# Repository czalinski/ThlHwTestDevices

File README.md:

# ThlHwTestDevices

KiCad designs, firmware and documentation for circuits that support testing of
electrical hardware, such as HASS and HALT testing.

Each design lives in its own folder under [`circuits/`](circuits/). Released
versions get separate folders with a version suffix (for example `V1p3` is
version 1.3), so every released version stays available side by side.

## License

Original work in this repository — the circuit designs, firmware and
documentation — is released under the [MIT License](LICENSE).

### Third-party files

The following are **not** covered by the MIT License. They remain under the
terms set by their original authors or providers:

* **`KiCad/` part libraries** (`footprints/`, `symbols/`,
  `SamacSys_Parts.pretty/`). Many of these footprints and symbols were
  downloaded from part-library services such as SnapEDA and SamacSys
  (Component Search Engine), or copied from the KiCad standard libraries.
  Check the provider's terms before redistributing them.
* **`Support/*.rar`**: setup and utility files for the T-962 reflow oven,
  included for convenience.
* **FatFs** in `circuits/ParasiticV1p0/firmware/lib/fatfs/`, by ChaN, under
  its own BSD-style license
  ([LICENSE.txt](circuits/ParasiticV1p0/firmware/lib/fatfs/LICENSE.txt)).

The PCB files (`*.kicad_pcb`) contain embedded copies of some of these
footprints, as all KiCad boards do. If you are a rights holder and believe a
file here should not be distributed, please open an issue.

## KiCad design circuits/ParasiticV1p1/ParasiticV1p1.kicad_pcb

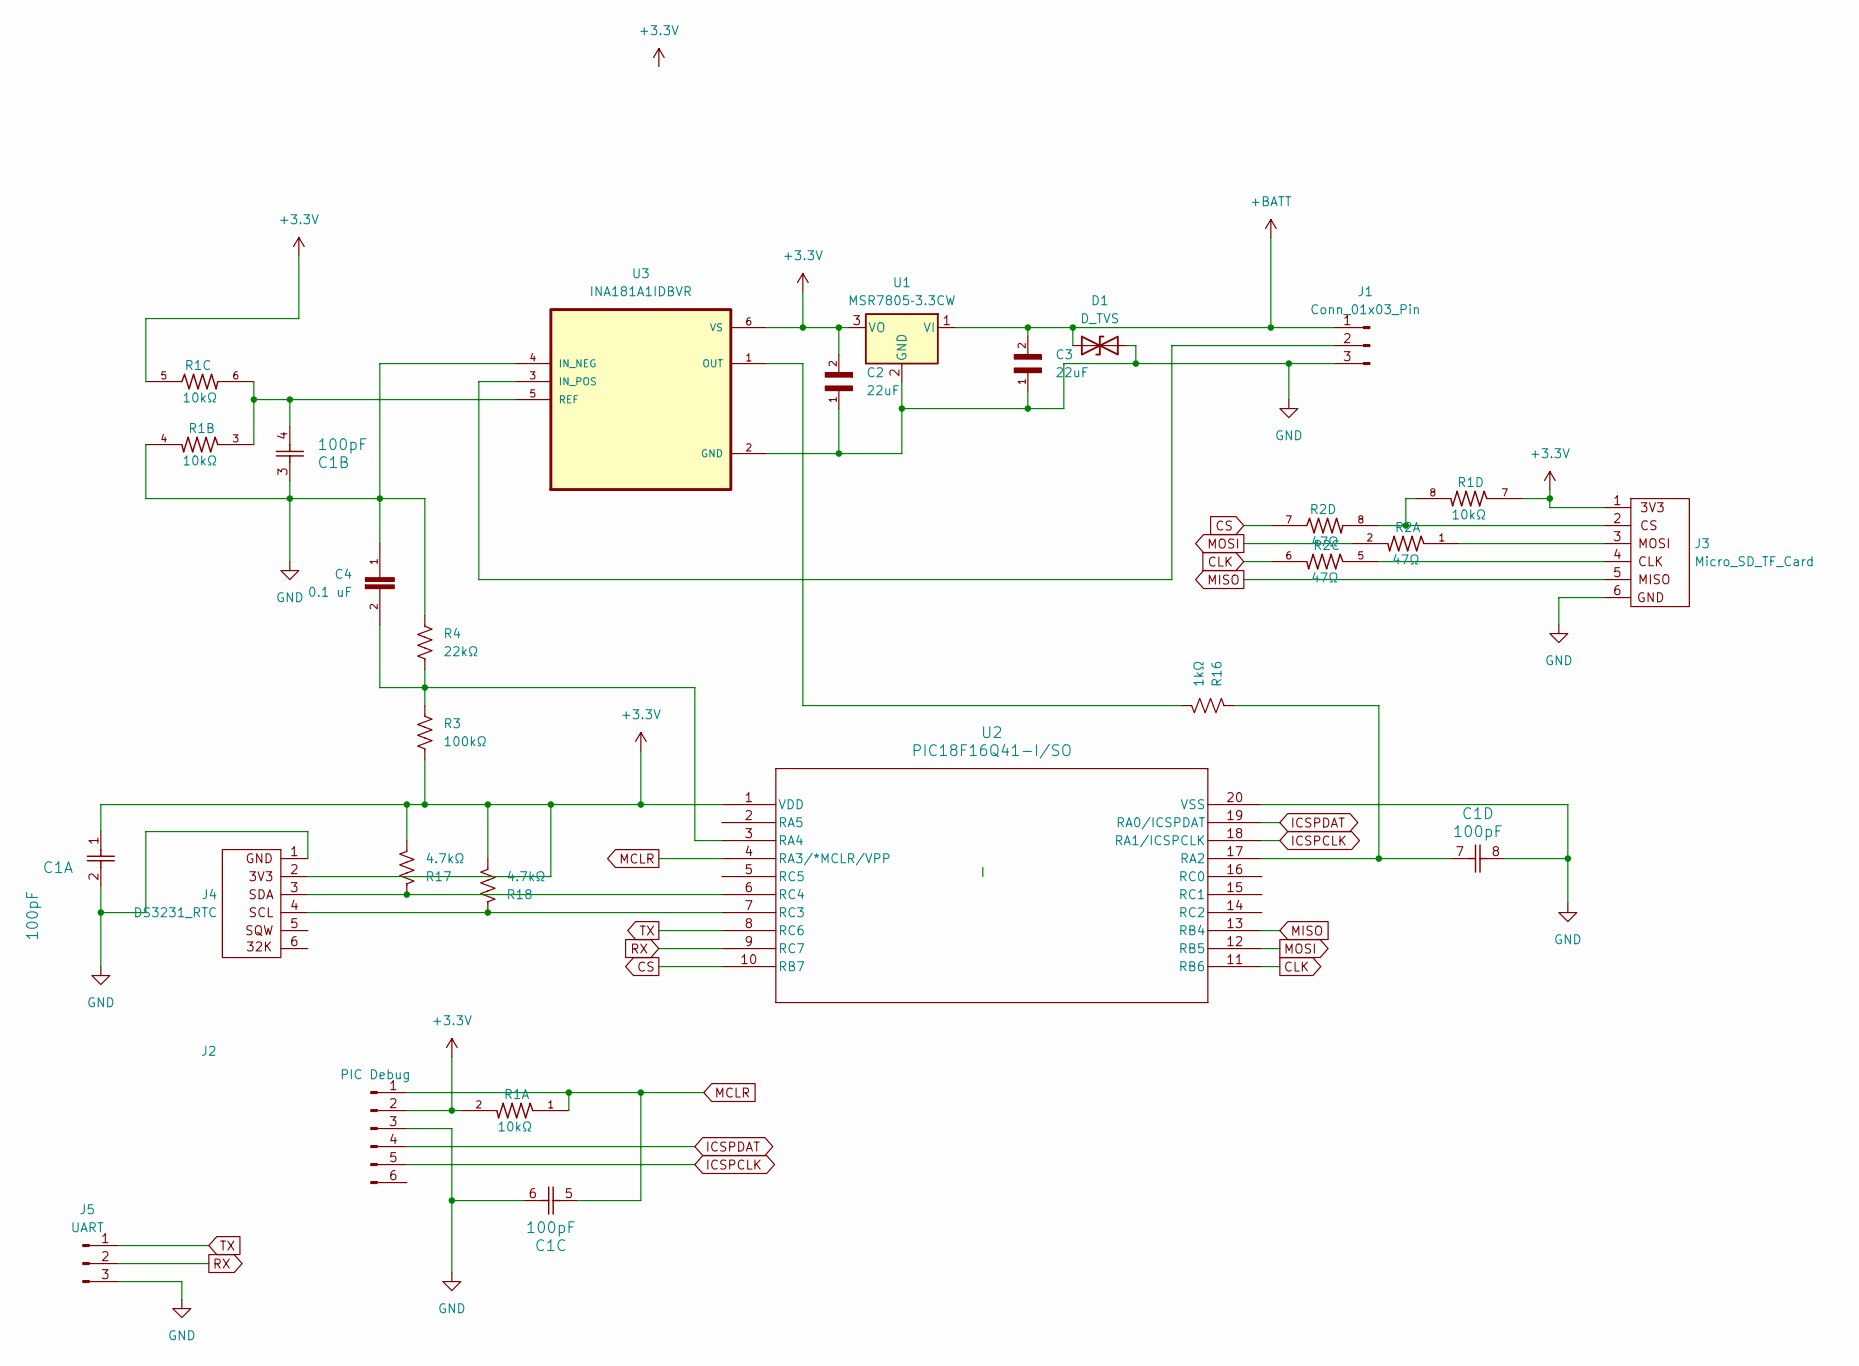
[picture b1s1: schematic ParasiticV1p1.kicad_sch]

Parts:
C1: 100pF; CAP_CA0612_3P2X1P6_YAG
C2, C3: 22uF; CAPC3225X270N
C4: 0.1 uF; DecouplingCapSMDLg
D1: D_TVS; D_SMC_Handsoldering
J1: Conn_01x03_Pin; PinHeader_1x03_P2.54mm_Vertical
J2: PIC Debug; PinHeader_1x06_P2.54mm_Horizontal
J3: Micro_SD_TF_Card
J4: DS3231_RTC; PinHeader_1x06_P2.54mm_Vertical
J5: UART; PinHeader_1x03_P2.54mm_Vertical
R1: 10kΩ; RESCAV80P320X160X70-8N
R2: 47Ω; RESCAV80P320X160X70-8N
R3: 100kΩ; RES_1206
R4: 22kΩ; RES_1206
R16: 1kΩ; RES_1206
R17, R18: 4.7kΩ; RES_1206
U1: MSR7805‑3.3CW; 3-SIP
U2: PIC18F16Q41-I/SO; SOIC20_SO_MCH
U3: INA181A1IDBVR; SOT95P280X145-6N

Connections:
+3.3V: C1.1, C2.2, J2.2, J3.1 (3V3), J4.2 (CS), R1.2, R1.5, R1.7, R3.2, R17.2, R18.2, U1.3 (VO), U2.1 (VDD), U3.6 (VS)
+BATT: C3.2, D1.1 (A1), J1.1, U1.1 (VI)
CLK: R2.6, U2.11 (RB6)
CS: R2.7, U2.10 (RB7)
GND: C1.2, C1.3, C1.6, C1.8, C2.1, C3.1, C4.1, D1.2 (A2), J1.3, J2.3, J3.6 (GND), J4.1 (3V3), J5.3, R1.4, R4.1, U1.2 (GND), U2.20 (VSS), U3.2 (GND), U3.4 (IN_NEG)
ICSPCLK: J2.5, U2.18 (RA1/ICSPCLK)
ICSPDAT: J2.4, U2.19 (RA0/ICSPDAT)
MCLR: C1.5, J2.1, R1.1, U2.4 (RA3/*MCLR/VPP)
MISO: J3.5 (MISO), U2.13 (RB4)
MOSI: R2.2, U2.12 (RB5)
unnamed: J1.2, U3.3 (IN_POS)
unnamed: J3.4 (CLK), R2.5
unnamed: J3.2 (CS), R1.8, R2.8
unnamed: J3.3 (MOSI), R2.1
unnamed: J4.4 (CLK), R18.1, U2.7 (RC3)
unnamed: J4.3 (MOSI), R17.1, U2.6 (RC4)
unnamed: C1.7, R16.1, U2.17 (RA2)
unnamed: C4.2, R3.1, R4.2, U2.3 (RA4)
unnamed: R16.2, U3.1 (OUT)
unnamed: C1.4, R1.3, R1.6, U3.5 (REF)
RX: J5.2, U2.9 (RC7)
TX: J5.1, U2.8 (RC6)

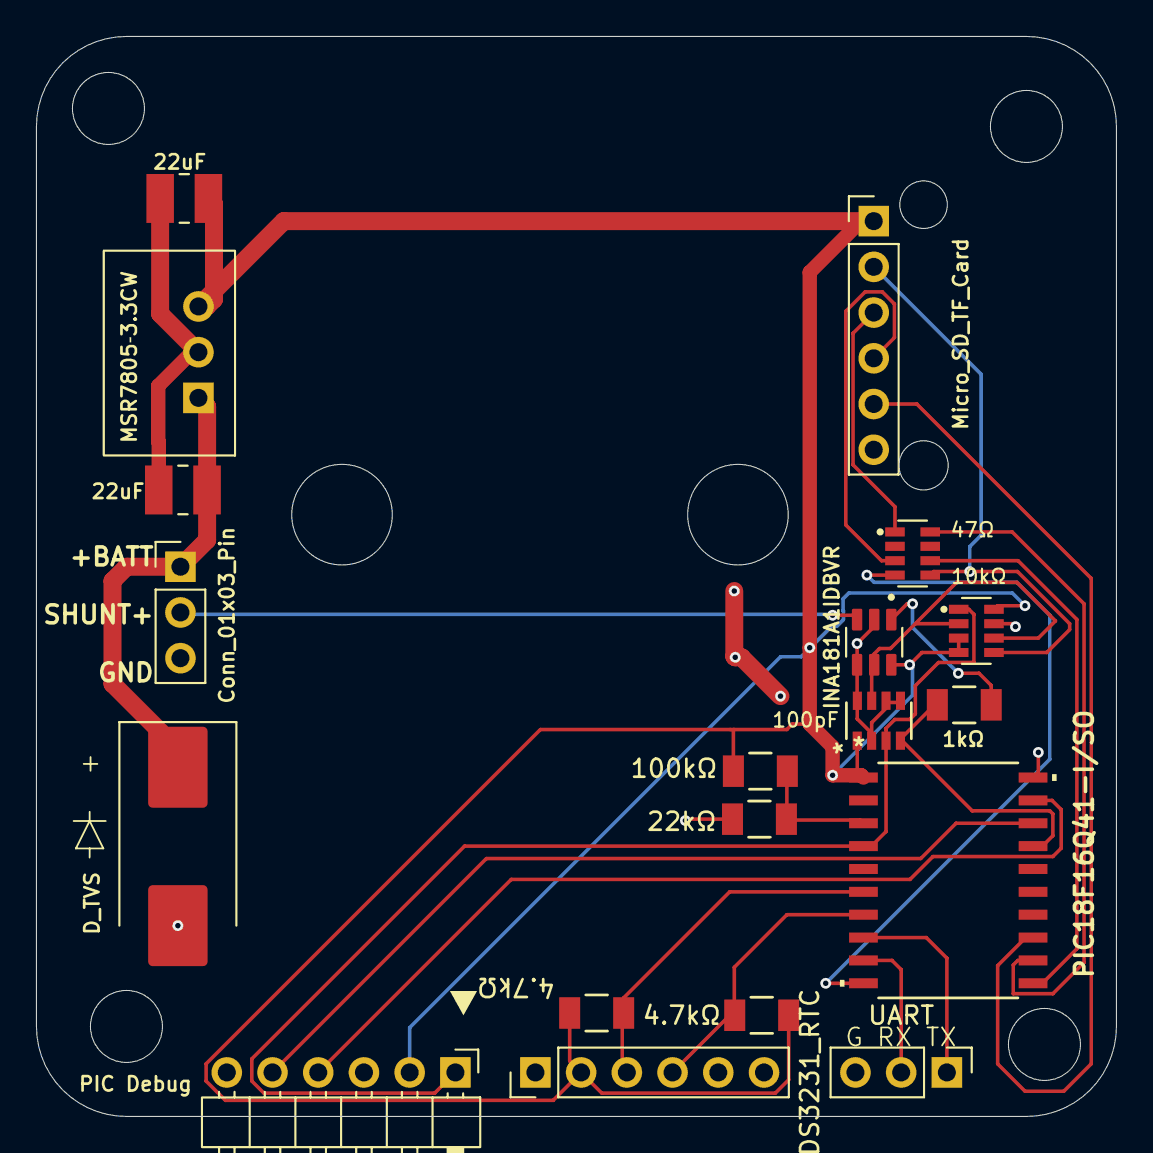
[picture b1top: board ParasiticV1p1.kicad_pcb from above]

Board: 2 copper layers, 60.0 x 60.0 mm, 19 parts (0 on the bottom side), 22 nets.

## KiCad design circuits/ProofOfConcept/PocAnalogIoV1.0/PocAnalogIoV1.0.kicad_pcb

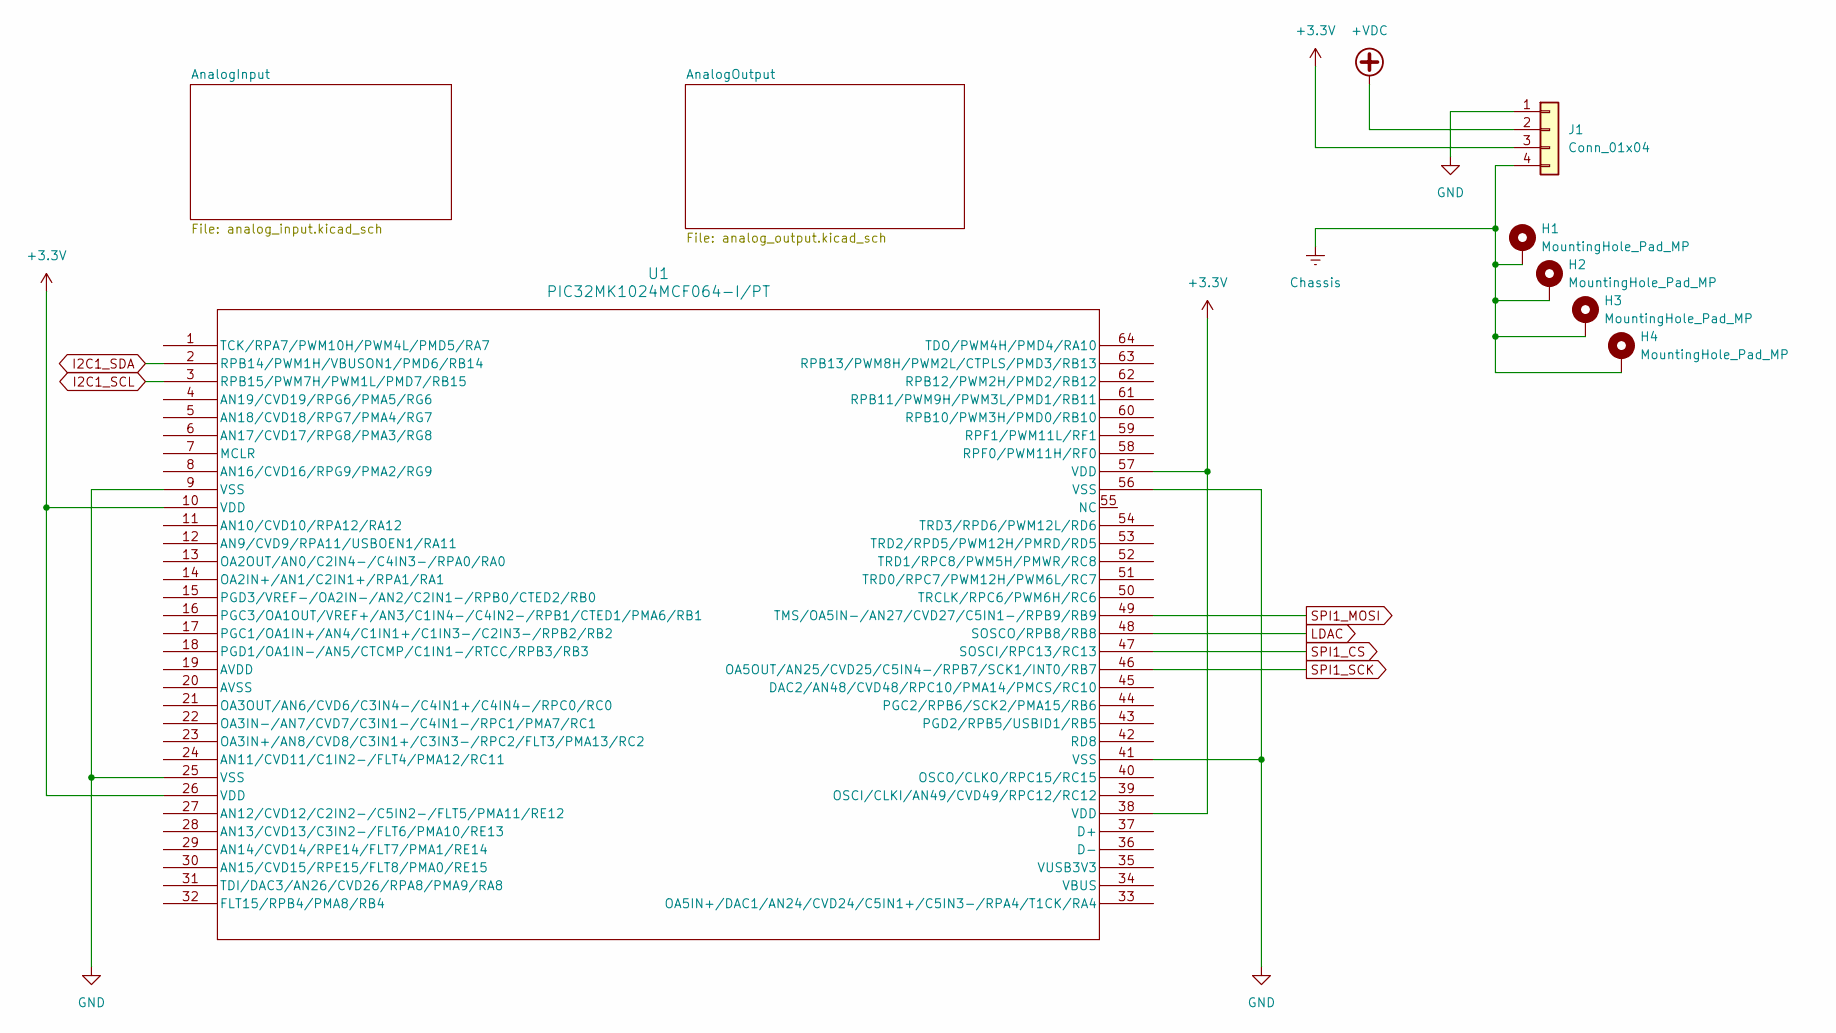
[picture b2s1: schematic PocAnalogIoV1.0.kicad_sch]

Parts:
H1, H2, H3, H4: MountingHole_Pad_MP; MountingHole_3.2mm_M3_Pad_Via
J1: Conn_01x04; PinHeader_1x04_P2.54mm_Vertical
U1: PIC32MK1024MCF064-I/PT; PIC64_Breakout

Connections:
+3.3V: J1.3, U1.10 (VDD), U1.26 (VDD), U1.38 (VDD), U1.57 (VDD); also elsewhere on the board
+VDC: J1.2; also elsewhere on the board
Chassis: H1.1 (MP_1), H2.1 (MP_1), H3.1 (MP_1), H4.1 (MP_1), J1.4
GND: J1.1, U1.9 (VSS), U1.25 (VSS), U1.41 (VSS), U1.56 (VSS); also elsewhere on the board
I2C1_SCL: U1.3 (RPB15/PWM7H/PWM1L/PMD7/RB15); also elsewhere on the board
I2C1_SDA: U1.2 (RPB14/PWM1H/VBUSON1/PMD6/RB14); also elsewhere on the board
LDAC: U1.48 (SOSCO/RPB8/RB8); also elsewhere on the board
SPI1_CS: U1.47 (SOSCI/RPC13/RC13); also elsewhere on the board
SPI1_MOSI: U1.49 (TMS/OA5IN-/AN27/CVD27/C5IN1-/RPB9/RB9); also elsewhere on the board
SPI1_SCK: U1.46 (OA5OUT/AN25/CVD25/C5IN4-/RPB7/SCK1/INT0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); also elsewhere on the board

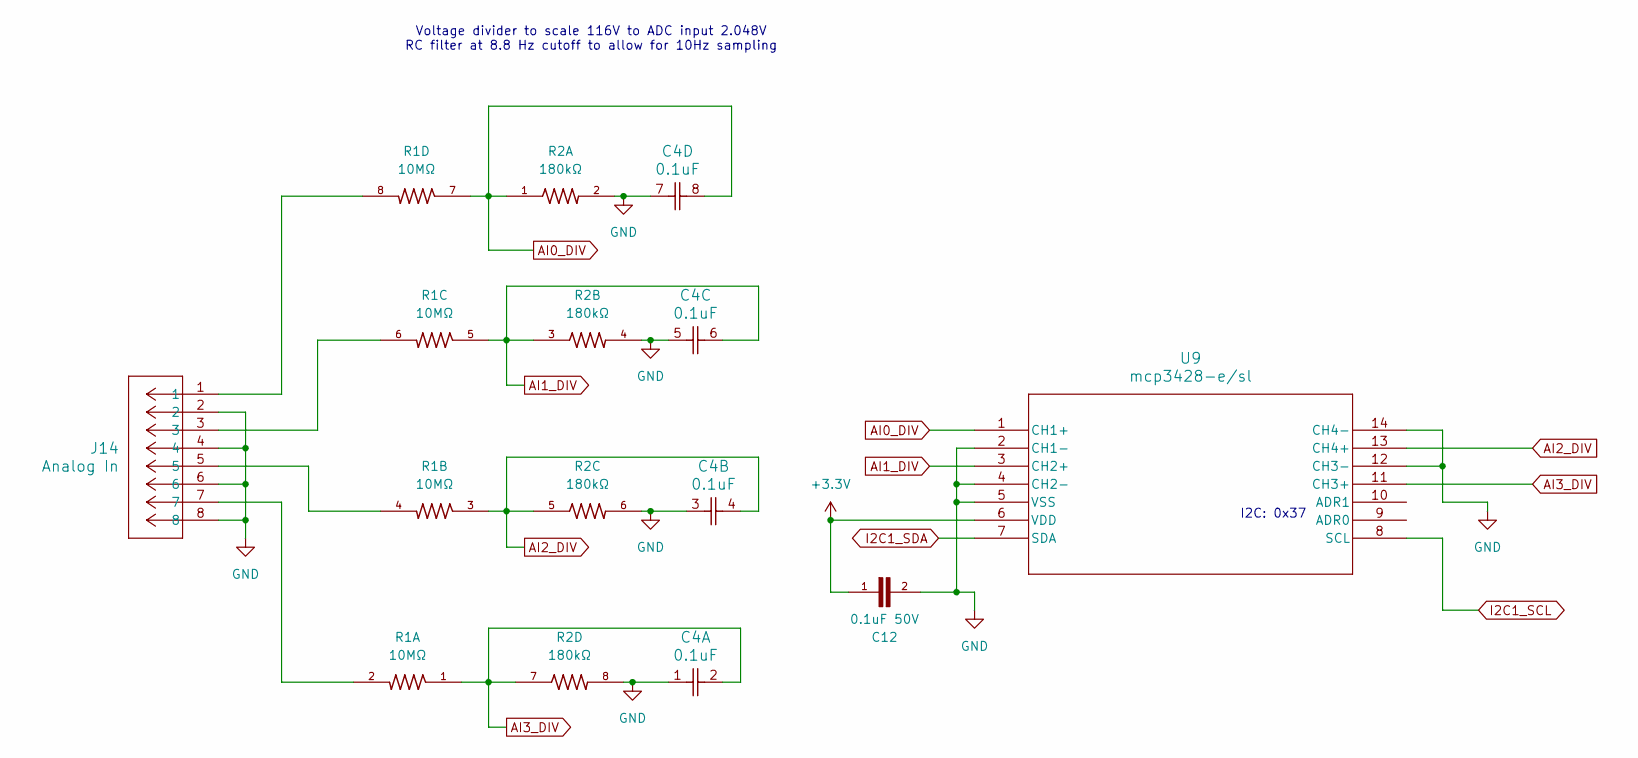
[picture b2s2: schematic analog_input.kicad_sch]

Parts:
C4: 0.1uF; CAP_CA0612_3P2X1P6_YAG
C12: 0.1uF 50V; CAPC2012X70
J14: Analog In; CONN_1989803_PXC
R1: 10MΩ; RESCAV80P320X160X70-8N
R2: 180kΩ; RESCAV80P320X160X70-8N
U9: mcp3428-e/sl; SOIC14-N_MC_MCH

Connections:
+3.3V: C12.1, U9.6 (VDD); also elsewhere on the board
AI0_DIV: C4.8, R1.7, R2.1, U9.1 (CH1+)
AI1_DIV: C4.6, R1.5, R2.3, U9.3 (CH2+)
AI2_DIV: C4.4, R1.3, R2.5, U9.13 (CH4+)
AI3_DIV: C4.2, R1.1, R2.7, U9.11 (CH3+)
GND: C4.1, C4.3, C4.5, C4.7, C12.2, J14.2, J14.4, J14.6, J14.8, R2.2, R2.4, R2.6, R2.8, U9.2 (CH1-), U9.4 (CH2-), U9.5 (VSS), U9.12 (CH3-), U9.14 (CH4-); also elsewhere on the board
I2C1_SCL: U9.8 (SCL); also elsewhere on the board
I2C1_SDA: U9.7 (SDA); also elsewhere on the board
unnamed: J14.1, R1.8
unnamed: J14.3, R1.6
unnamed: J14.5, R1.4
unnamed: J14.7, R1.2

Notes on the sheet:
I2C: 0x37
Voltage divider to scale 116V to ADC input 2.048V RC filter at 8.8 Hz cutoff to allow for 10Hz sampling

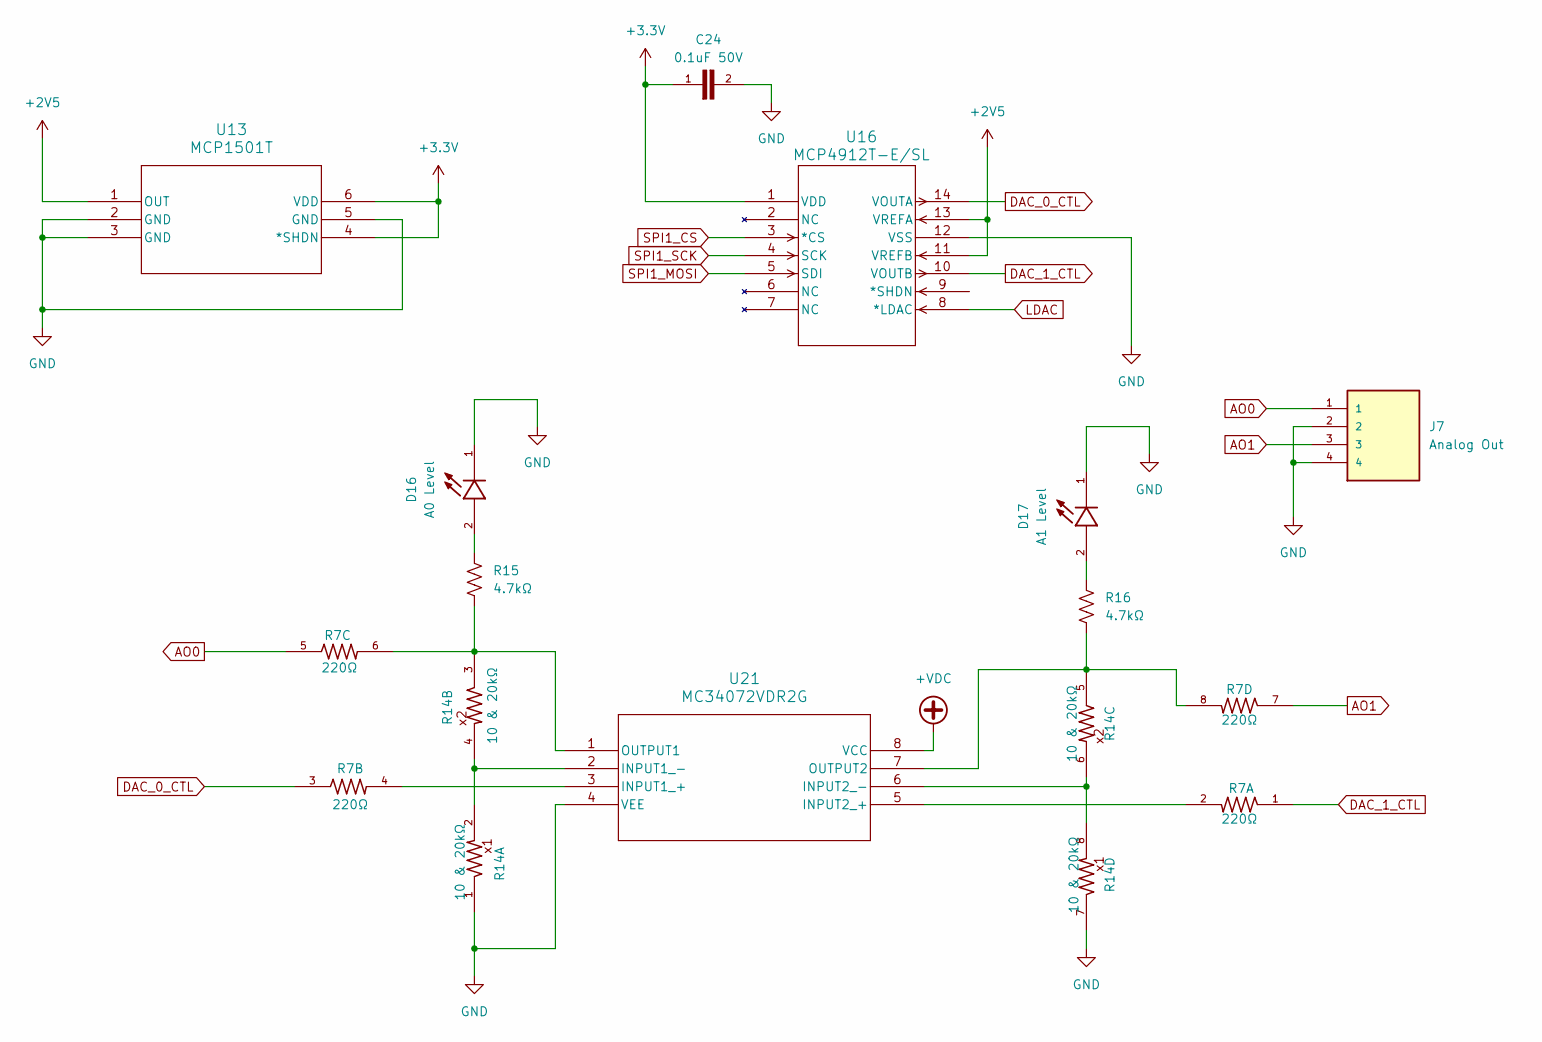
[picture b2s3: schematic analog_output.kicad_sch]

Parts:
C24: 0.1uF 50V; CAPC2012X70
D16: A0 Level; LED_LTST-C170GKT; PARTREV I
D17: A1 Level; LED_LTST-C170GKT; PARTREV I
J7: Analog Out; TE_1985218; PARTREV 29.03.2021
R7: 220Ω; RESCAV80P320X160X70-8N
R14: 10 & 20kΩ; RESCAV80P320X160X70-8N
R15, R16: 4.7kΩ; RES_1206
U13: MCP1501T; SOT-23_OT&slash_OTY_MCH
U16: MCP4912T-E/SL; SOIC14-N_MC_MCH
U21: MC34072VDR2G; SOIC8_ONS

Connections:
+2V5: U13.1 (OUT), U16.11 (VREFB), U16.13 (VREFA)
+3.3V: C24.1, U13.4 (*SHDN), U13.6 (VDD), U16.1 (VDD); also elsewhere on the board
+VDC: U21.8 (VCC); also elsewhere on the board
AO0: J7.1, R7.5
AO1: J7.3, R7.7
DAC_0_CTL: R7.3, U16.14 (VOUTA)
DAC_1_CTL: R7.1, U16.10 (VOUTB)
GND: C24.2, D16.1, D17.1, J7.2, J7.4, R14.1, R14.7, U13.2 (GND), U13.3 (GND), U13.5 (GND), U16.12 (VSS), U21.4 (VEE); also elsewhere on the board
LDAC: U16.8 (*LDAC); also elsewhere on the board
unnamed: D16.2, R15.1
unnamed: D17.2, R16.1
unnamed: R7.4, U21.3 (INPUT1_+)
unnamed: R14.2, R14.4, U21.2 (INPUT1_-)
unnamed: R7.2, U21.5 (INPUT2_+)
unnamed: R14.6, R14.8, U21.6 (INPUT2_-)
unnamed: R7.6, R14.3, R15.2, U21.1 (OUTPUT1)
unnamed: R7.8, R14.5, R16.2, U21.7 (OUTPUT2)
SPI1_CS: U16.3 (*CS); also elsewhere on the board
SPI1_MOSI: U16.5 (SDI); also elsewhere on the board
SPI1_SCK: U16.4 (SCK); also elsewhere on the board

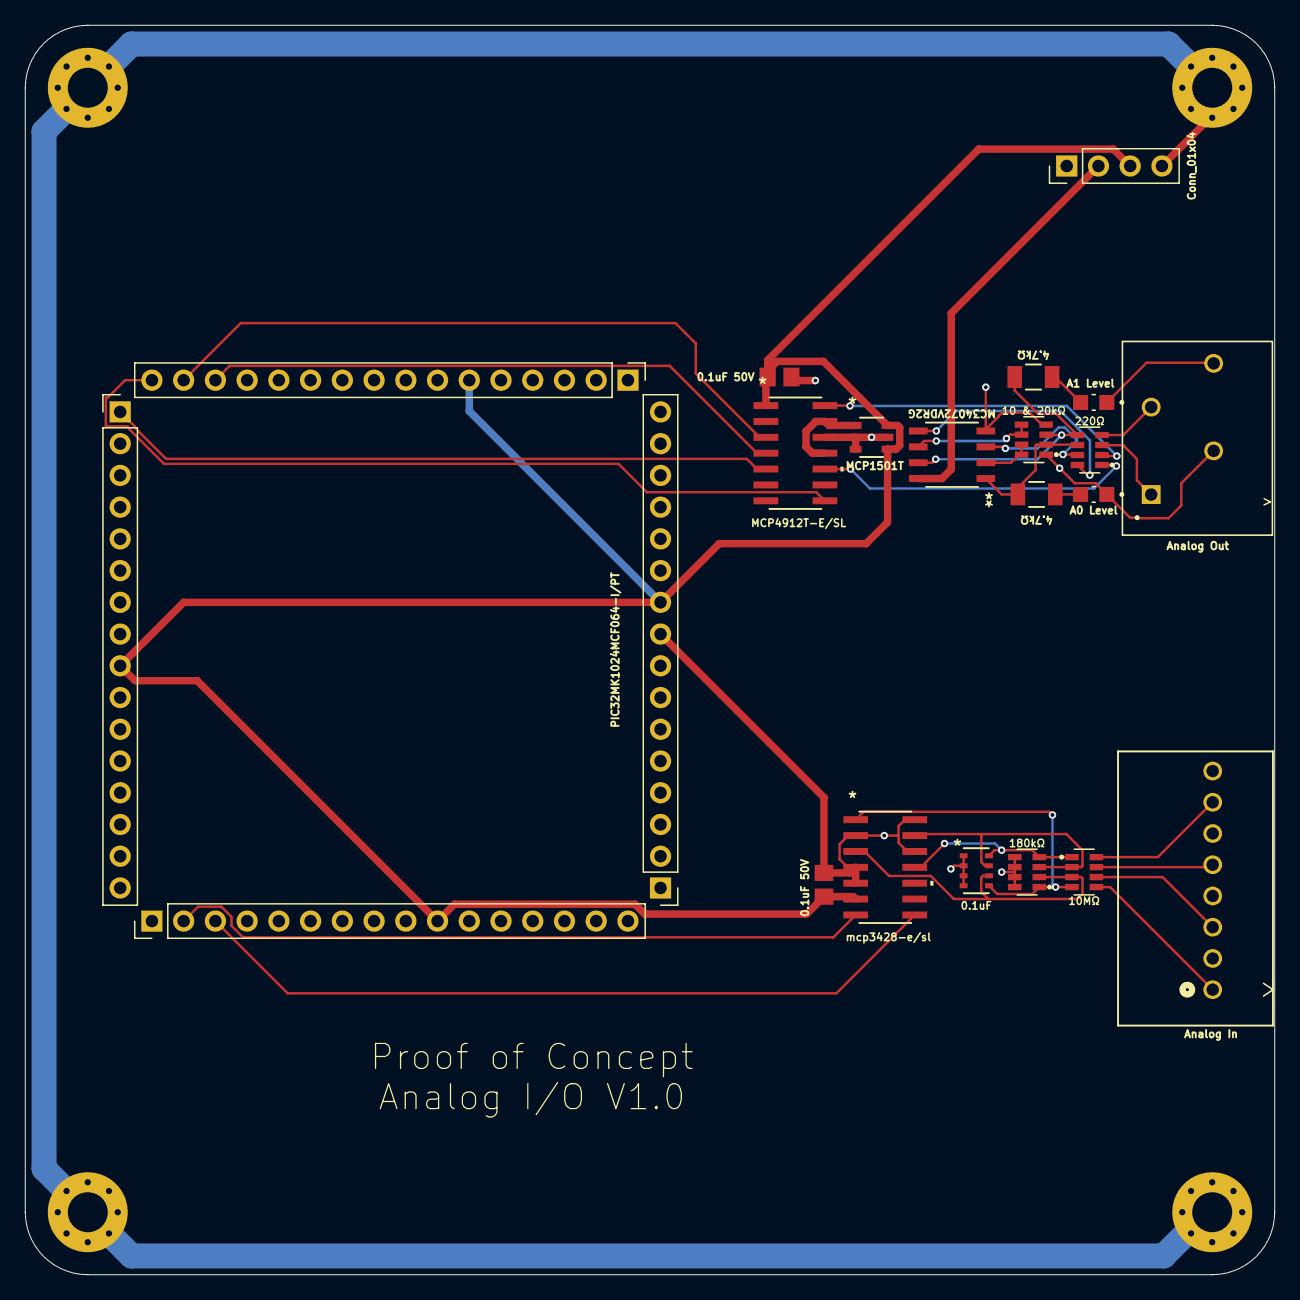
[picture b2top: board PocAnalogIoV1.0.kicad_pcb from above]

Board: 2 copper layers, 100.0 x 100.0 mm, 23 parts (0 on the bottom side), 31 nets.

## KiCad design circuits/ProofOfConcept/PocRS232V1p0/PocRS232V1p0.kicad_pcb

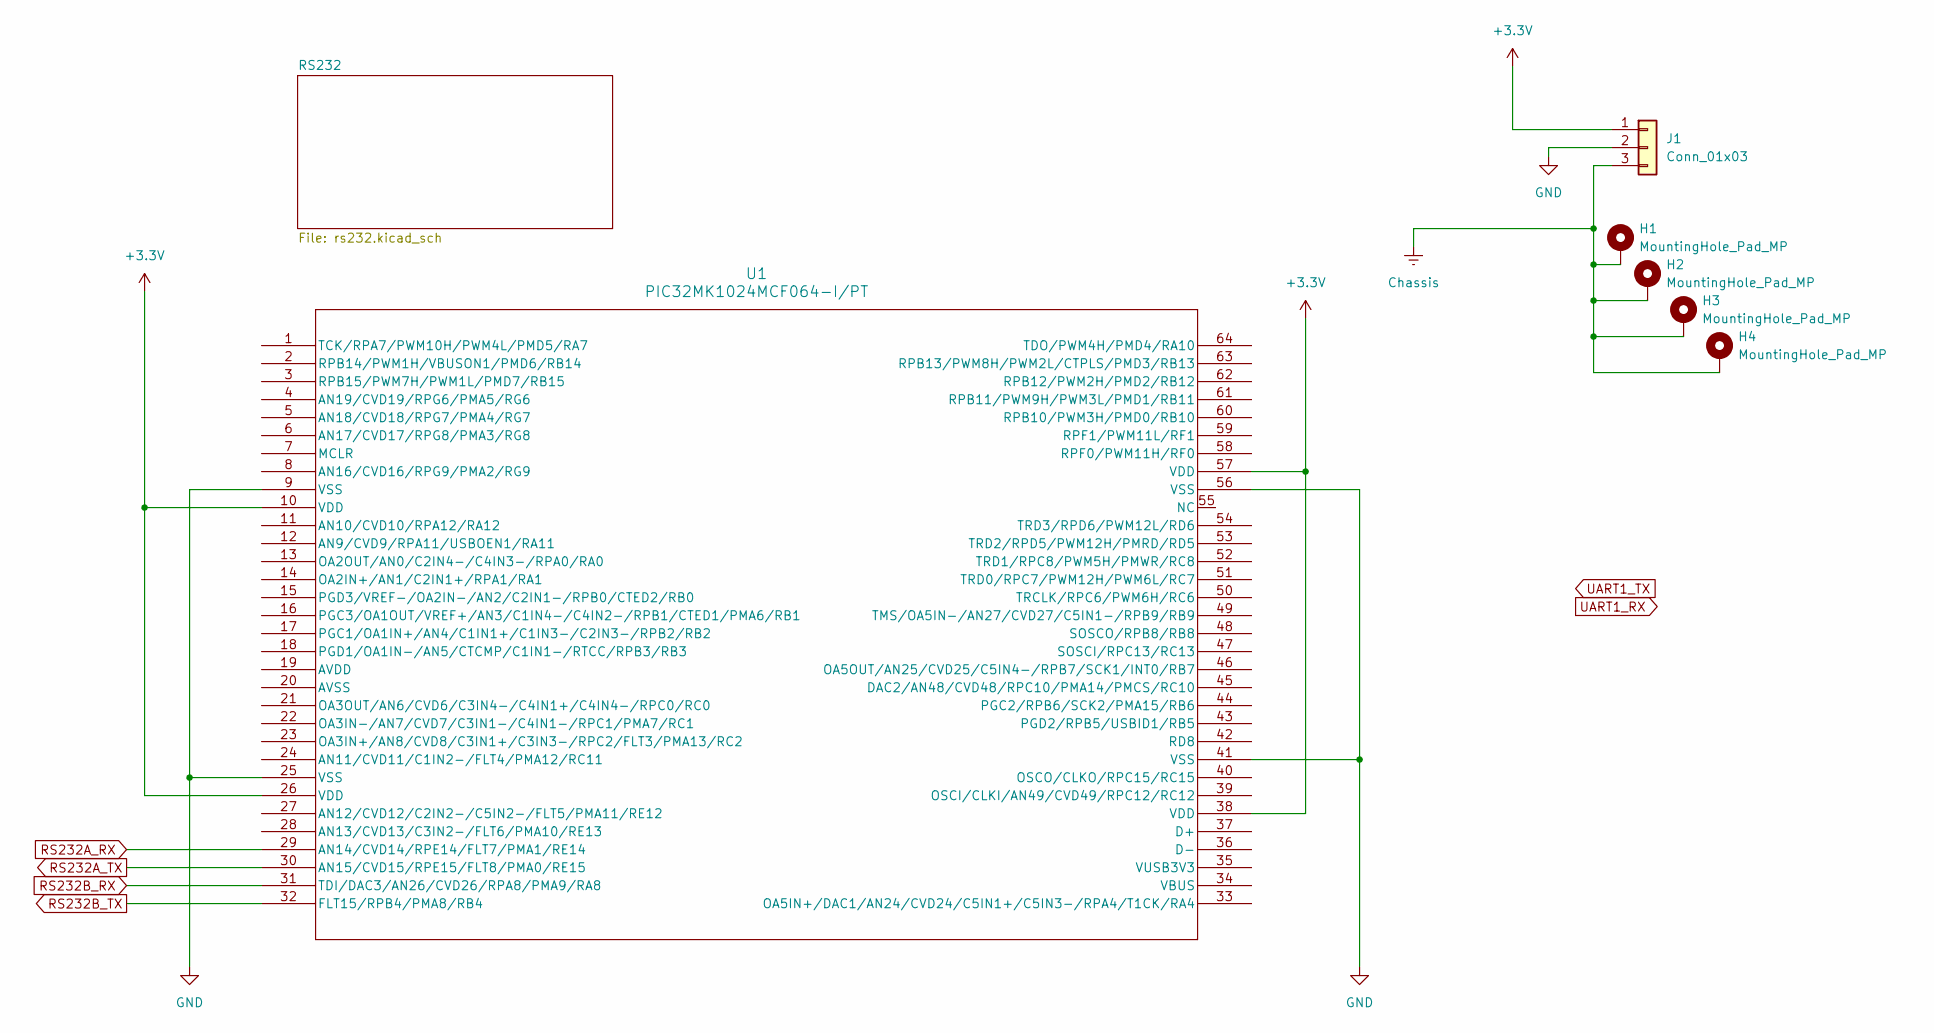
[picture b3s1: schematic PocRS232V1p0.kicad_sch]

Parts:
H1, H2, H3, H4: MountingHole_Pad_MP; MountingHole_3.2mm_M3_Pad_Via
J1: Conn_01x03; PinHeader_1x03_P2.54mm_Vertical
U1: PIC32MK1024MCF064-I/PT; PIC64_Breakout

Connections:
+3.3V: J1.1, U1.10 (VDD), U1.26 (VDD), U1.38 (VDD), U1.57 (VDD); also elsewhere on the board
Chassis: H1.1 (MP_1), H2.1 (MP_1), H3.1 (MP_1), H4.1 (MP_1), J1.3; also elsewhere on the board
GND: J1.2, U1.9 (VSS), U1.25 (VSS), U1.41 (VSS), U1.56 (VSS); also elsewhere on the board
RS232A_RX: U1.29 (AN14/CVD14/RPE14/FLT7/PMA1/RE14); also elsewhere on the board
RS232A_TX: U1.30 (AN15/CVD15/RPE15/FLT8/PMA0/RE15); also elsewhere on the board
RS232B_RX: U1.31 (TDI/DAC3/AN26/CVD26/RPA8/PMA9/RA8); also elsewhere on the board
RS232B_TX: U1.32 (FLT15/RPB4/PMA8/RB4); also elsewhere on the board

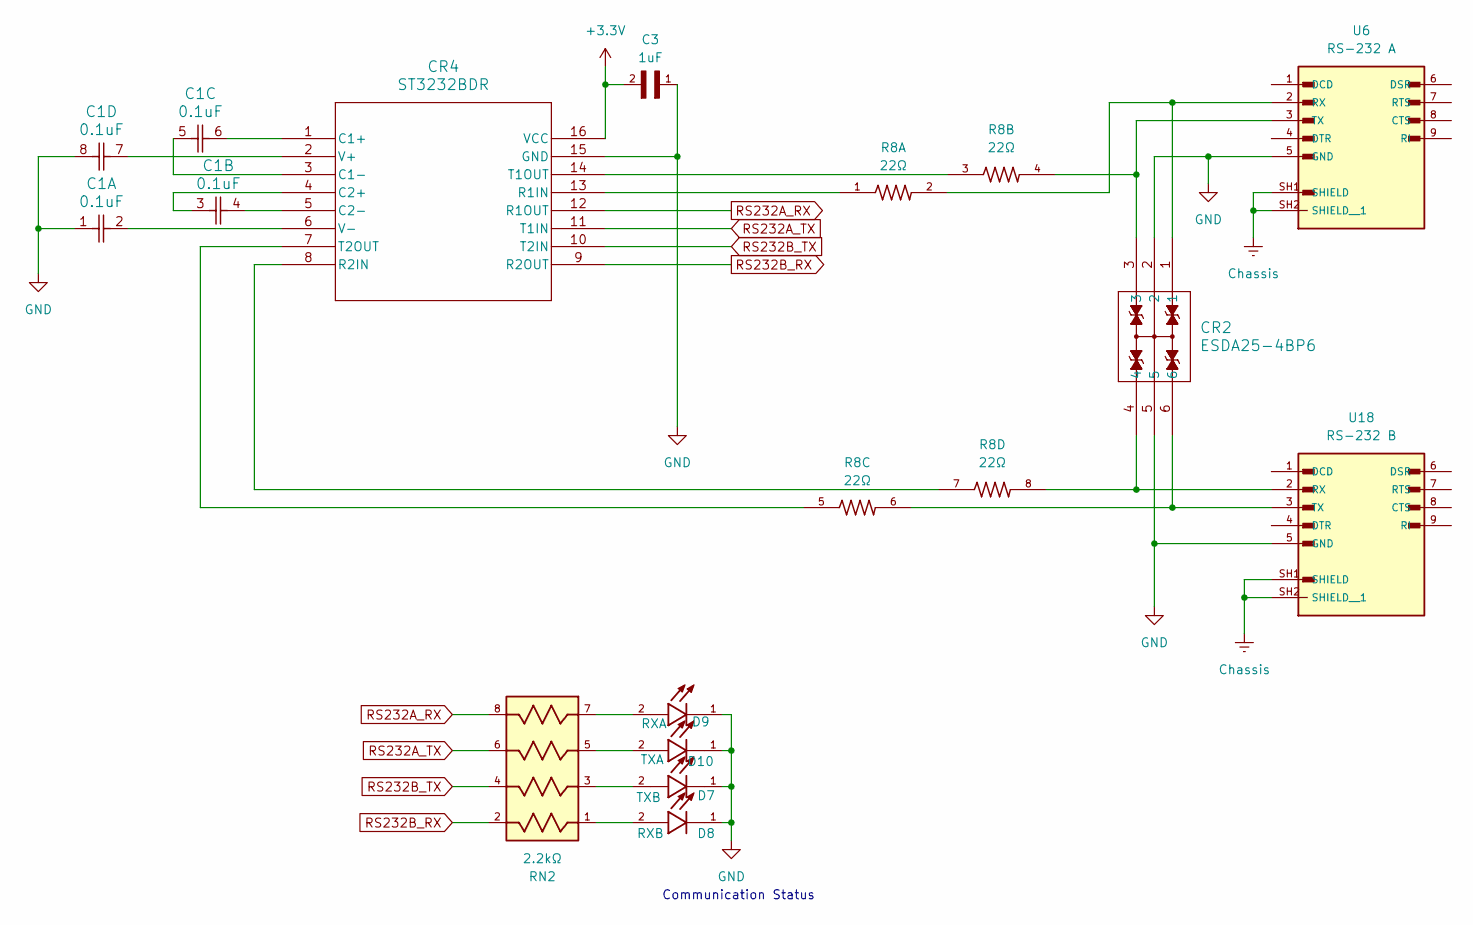
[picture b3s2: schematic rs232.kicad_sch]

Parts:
C1: 0.1uF; CAP_CA0612_3P2X1P6_YAG
C3: 1uF; CAPC1608X90N
CR2: ESDA25-4BP6; SOT666_ESDA25_STM
CR4: ST3232BDR; SO-16_STM
D7: TXB; LED_LTST-C170GKT; PARTREV I
D8: RXB; LED_LTST-C170GKT; PARTREV I
D9: RXA; LED_LTST-C170GKT; PARTREV I
D10: TXA; LED_LTST-C170GKT; PARTREV I
R8: 22Ω; RESCAV80P320X160X70-8N
RN2: 2.2kΩ; RESCAXS50P200X100X55-8N
U6: RS-232 A; ASSMANN_A-DS_09_A_KG-T2S
U18: RS-232 B; ASSMANN_A-DS_09_A_KG-T2S

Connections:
+3.3V: C3.2, CR4.16 (VCC); also elsewhere on the board
Chassis: U6.SH1 (SHIELD), U6.SH2 (SHIELD__1), U18.SH1 (SHIELD), U18.SH2 (SHIELD__1); also elsewhere on the board
GND: C1.1, C1.8, C3.1, CR2.2, CR2.5, CR4.15 (GND), D7.1, D8.1, D9.1, D10.1, U6.5 (GND), U18.5 (GND); also elsewhere on the board
unnamed: C1.6, CR4.1 (C1+)
unnamed: C1.5, CR4.3 (C1-)
unnamed: C1.3, CR4.4 (C2+)
unnamed: C1.4, CR4.5 (C2-)
unnamed: CR4.13 (R1IN), R8.1
unnamed: CR4.8 (R2IN), R8.7
unnamed: CR4.14 (T1OUT), R8.3
unnamed: CR4.7 (T2OUT), R8.5
unnamed: C1.7, CR4.2 (V+)
unnamed: C1.2, CR4.6 (V-)
unnamed: D7.2, RN2.3
unnamed: D8.2, RN2.1
unnamed: D9.2, RN2.7
unnamed: D10.2, RN2.5
unnamed: CR2.1, R8.2, U6.2 (RX)
unnamed: CR2.3, R8.4, U6.3 (TX)
unnamed: CR2.4, R8.8, U18.2 (RX)
unnamed: CR2.6, R8.6, U18.3 (TX)
RS232A_RX: CR4.12 (R1OUT), RN2.8; also elsewhere on the board
RS232A_TX: CR4.11 (T1IN), RN2.6; also elsewhere on the board
RS232B_RX: CR4.9 (R2OUT), RN2.2; also elsewhere on the board
RS232B_TX: CR4.10 (T2IN), RN2.4; also elsewhere on the board

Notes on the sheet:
Communication Status

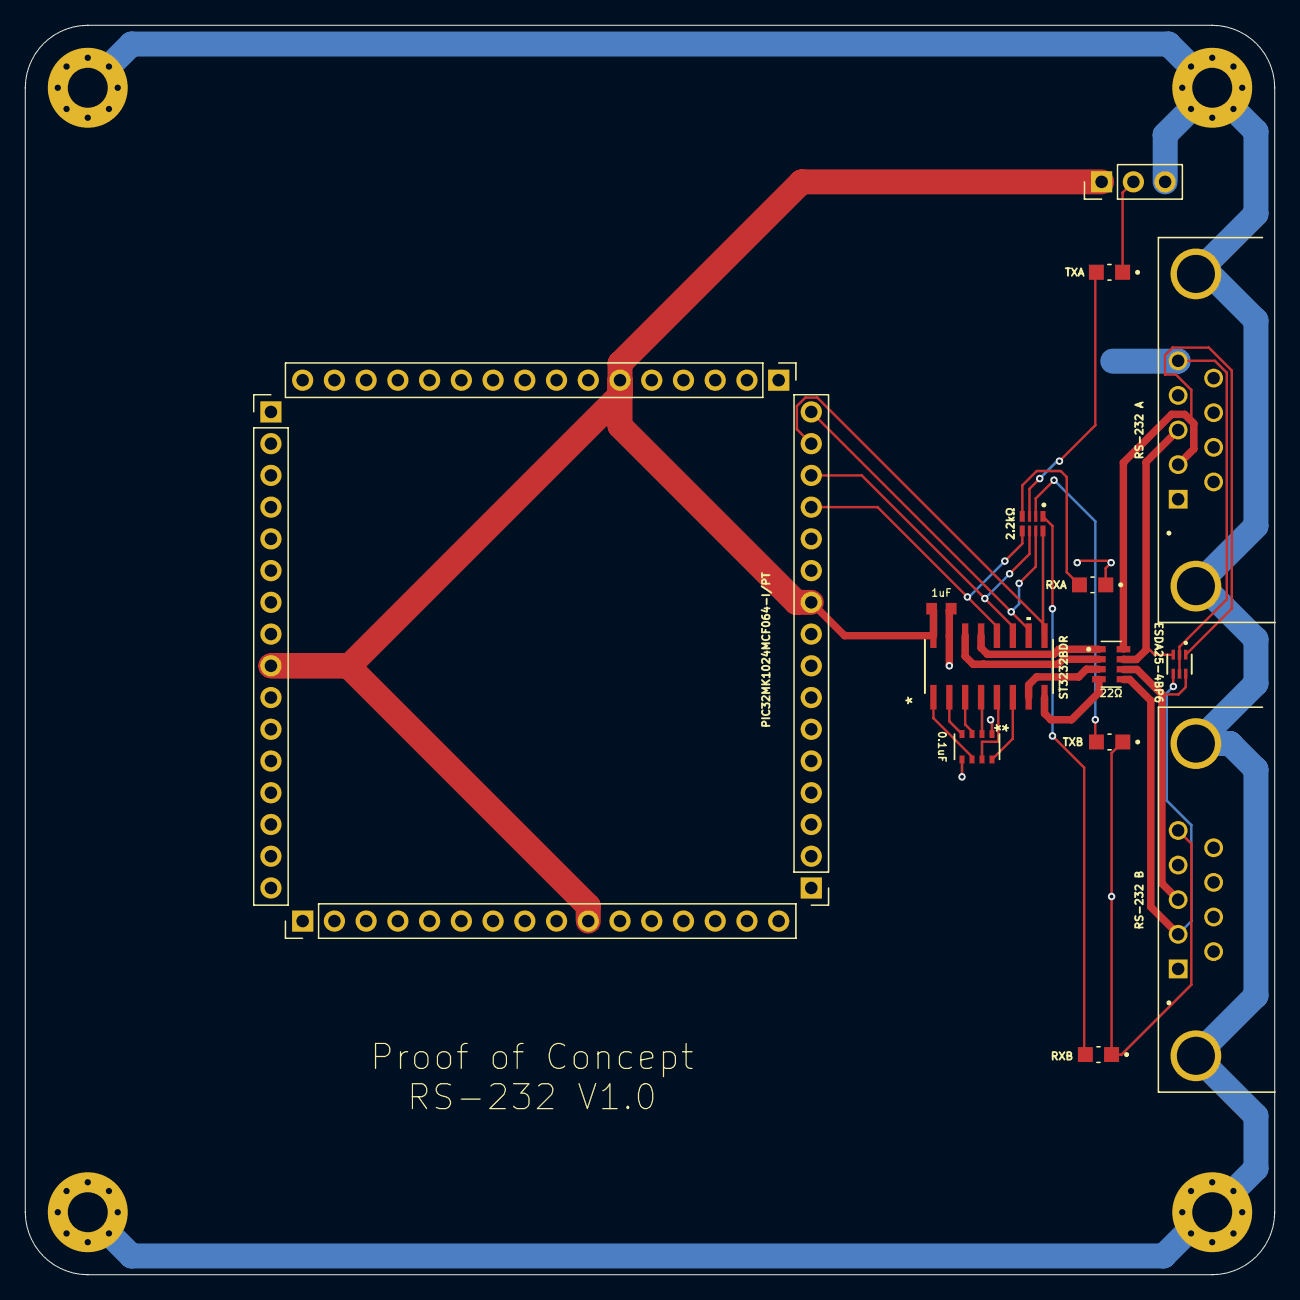
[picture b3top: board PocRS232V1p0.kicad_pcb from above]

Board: 2 copper layers, 100.0 x 100.0 mm, 18 parts (0 on the bottom side), 25 nets.
